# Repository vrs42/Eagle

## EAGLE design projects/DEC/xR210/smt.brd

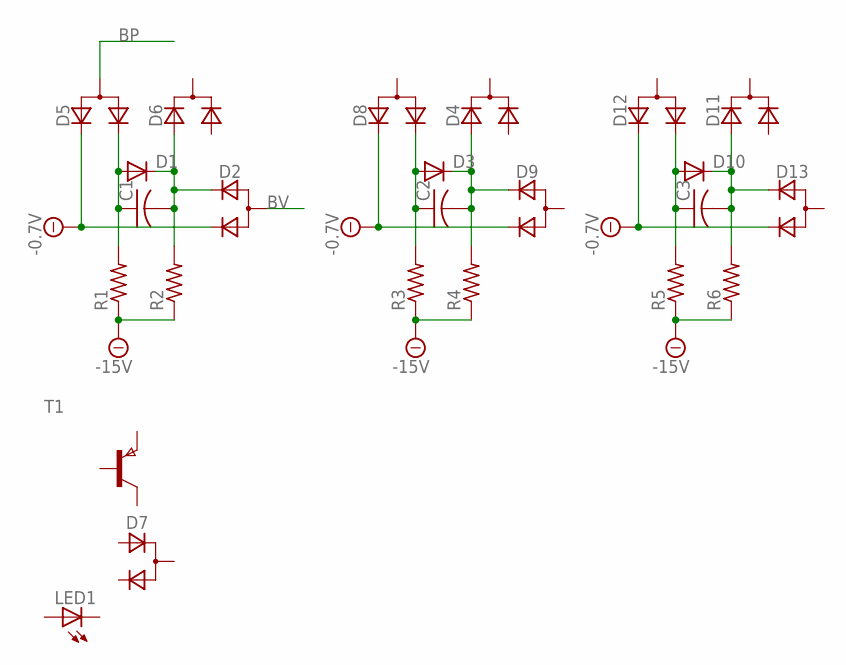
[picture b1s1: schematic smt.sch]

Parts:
C1, C2, C3: C-USC0603; C0603
D1, D3, D10: DIODE-SOD323-R; SOD323-R
D2, D5, D8, D9, D12, D13: D_2CSOT323; SOT323
D4, D6, D11: D_2ASOT323; SOT323
D7: D_ACACSOT323; SOT323
LED1: LEDCHIPLED_0603; CHIPLED_0603
R1, R2, R3, R4, R5, R6: R-US_R0603; R0603
T1: PNPSOT323; SOT323

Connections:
-1V: D2.3 (C2), D5.2 (C1), D8.2 (C1), D9.3 (C2), D12.2 (C1), D13.3 (C2)
-15V: R1.1, R2.1, R3.1, R4.1, R5.1, R6.1
BP: D5.1 (A)
BV: D2.1 (A)
unnamed: C1.1, D1.A, D5.3 (C2), R1.2
unnamed: C1.2, D1.C, D2.2 (C1), D6.2 (A1), R2.2
unnamed: C2.1, D3.A, D8.3 (C2), R3.2
unnamed: C2.2, D3.C, D4.2 (A1), D9.2 (C1), R4.2
unnamed: C3.1, D10.A, D12.3 (C2), R5.2
unnamed: C3.2, D10.C, D11.2 (A1), D13.2 (C1), R6.2

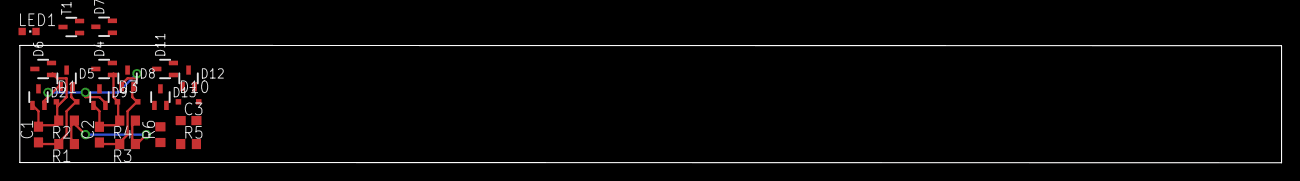
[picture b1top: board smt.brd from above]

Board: 2 copper layers, 136.7 x 12.7 mm, 24 parts (0 on the bottom side), 8 nets.

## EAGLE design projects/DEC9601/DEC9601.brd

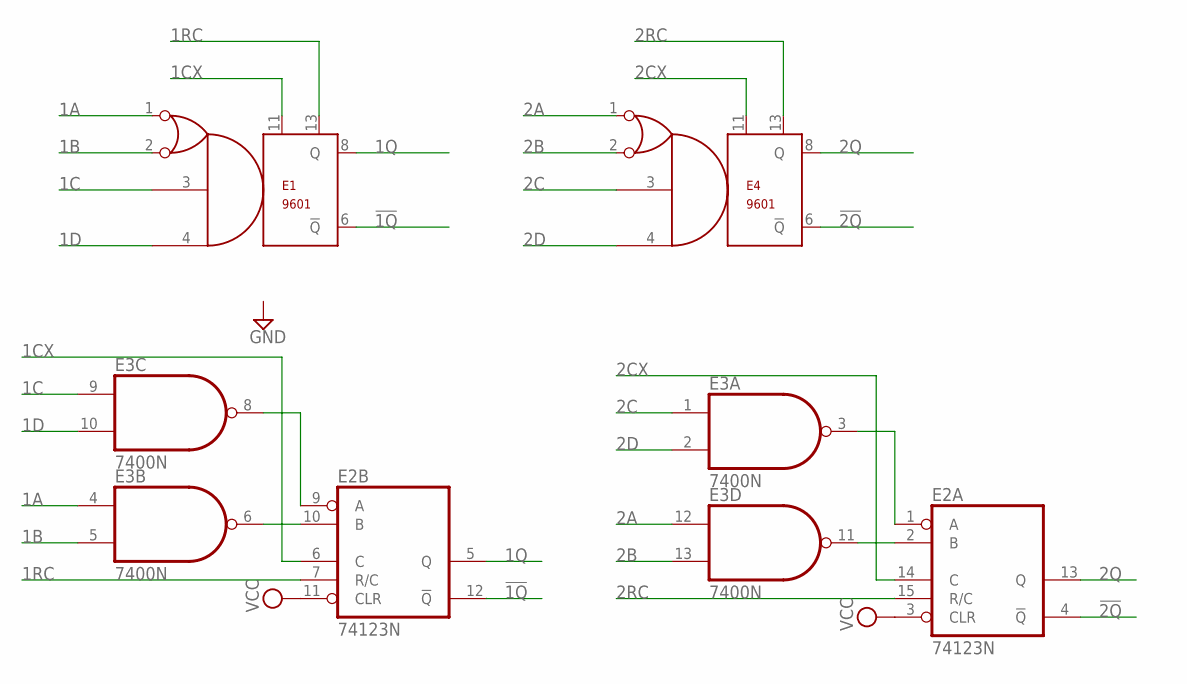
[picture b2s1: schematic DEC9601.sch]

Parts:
E1, E4: 9601; DIL14
E2: 74123N; DIL16
E3: 7400N; DIL14

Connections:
1A: E1.1, E3.4 (I0)
1B: E1.2, E3.5 (I1)
1C: E1.3, E3.9 (I0)
1CX: E1.11, E2.6 (C)
1D: E1.4, E3.10 (I1)
1Q: E1.8 (Q), E2.5 (Q)
1RC: E1.13, E2.7 (R/C)
2A: E3.12 (I0), E4.1
2B: E3.13 (I1), E4.2
2C: E3.1 (I0), E4.3
2CX: E2.14 (C), E4.11
2D: E3.2 (I1), E4.4
2Q: E2.13 (Q), E4.8 (Q)
2RC: E2.15 (R/C), E4.13
!1Q: E1.6 (!Q), E2.12 (!Q)
!2Q: E2.4 (!Q), E4.6 (!Q)
GND: E1.7 (GND), E2.8 (GND), E3.7 (GND), E4.7 (GND)
unnamed: E2.10 (B), E3.6 (O)
unnamed: E2.9 (A), E3.8 (O)
unnamed: E2.1 (A), E3.3 (O)
unnamed: E2.2 (B), E3.11 (O)
VCC: E1.14 (VCC), E2.3 (CLR), E2.11 (CLR), E2.16 (VCC), E3.14 (VCC), E4.14 (VCC)

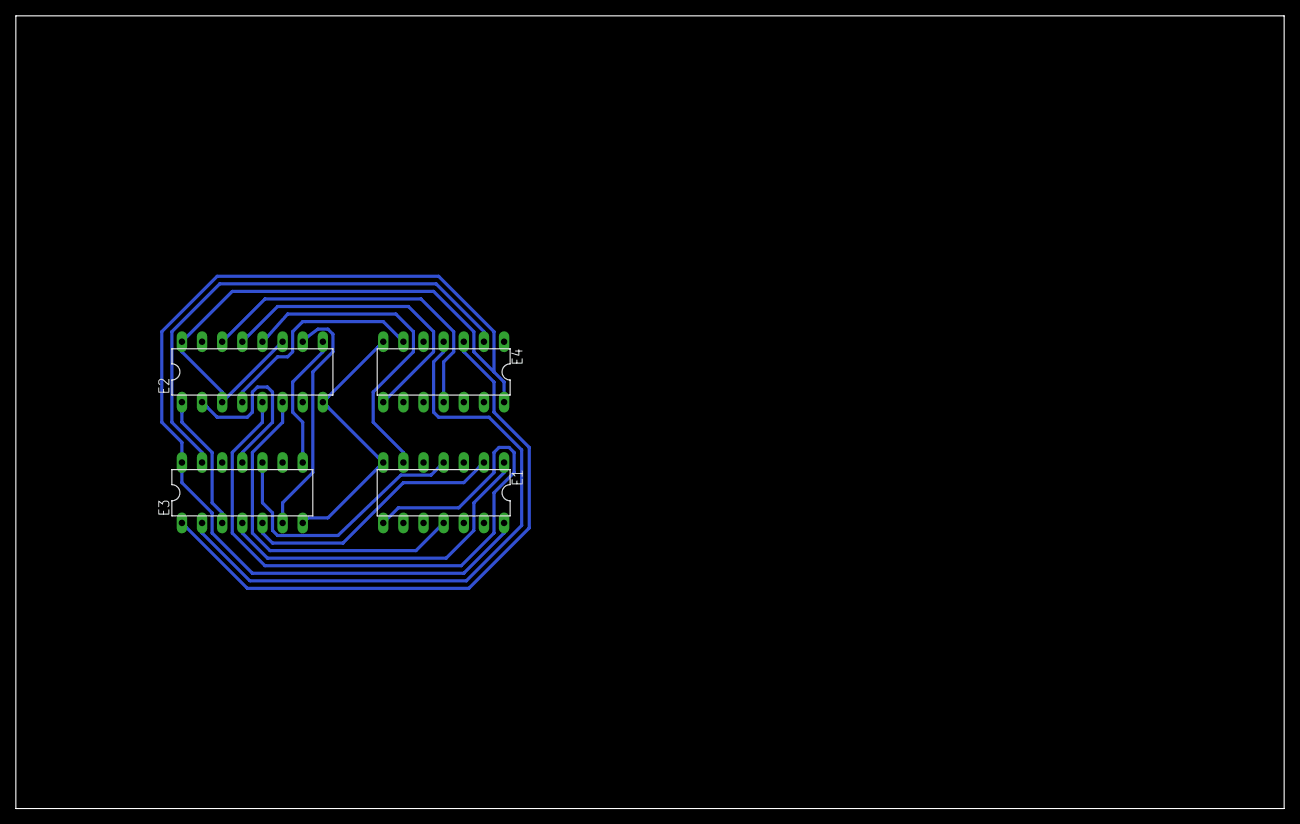
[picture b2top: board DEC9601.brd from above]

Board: 2 copper layers, 160.0 x 100.0 mm, 4 parts (0 on the bottom side), 22 nets.

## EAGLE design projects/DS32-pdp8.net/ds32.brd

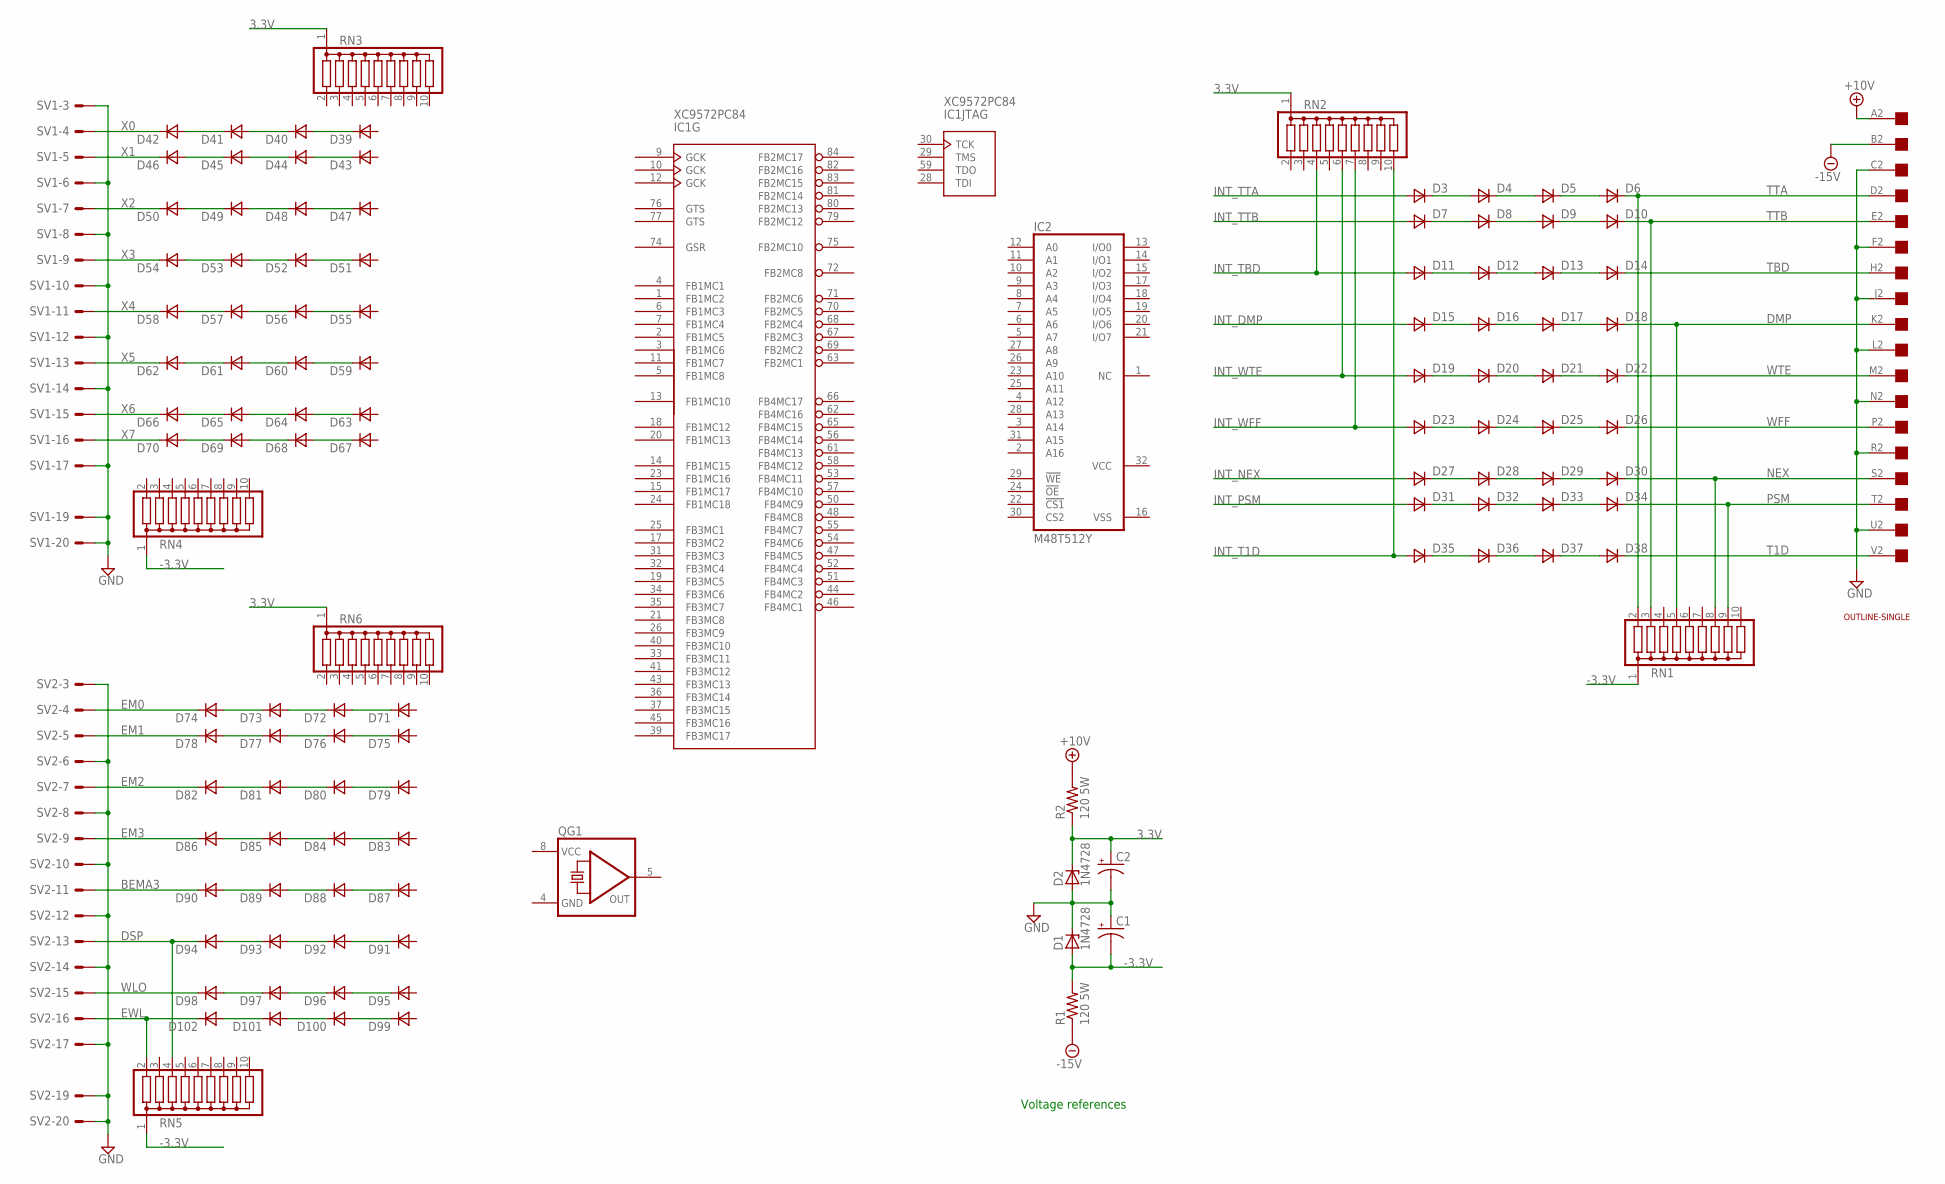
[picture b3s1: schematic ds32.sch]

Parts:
C1, C2: CPOL-USE15-5AXIAL; E15-5
D1, D2: 1N4728; DO41Z10
D3, D4, D5, D6, D7, D8, D9, D10, D11, D12, D13, D14, D15, D16, D17, D18, D19, D20, D21, D22, D23, D24, D25, D26, D27, D28, D29, D30, D31, D32, D33, D34, D35, D36, D37, D38, D39, D40, D41, D42, D43, D44, D45, D46, D47, D48, D49, D50, D51, D52, D53, D54, D55, D56, D57, D58, D59, D60, D61, D62, D63, D64, D65, D66, D67, D68, D69, D70, D71, D72, D73, D74, D75, D76, D77, D78, D79, D80, D81, D82, D83, D84, D85, D86, D87, D88, D89, D90, D91, D92, D93, D94, D95, D96, D97, D98, D99, D100, D101, D102: DSOD323; SOD323
IC1: XC9572PC84; PLCC-S84
IC2: M48T512Y; DIL32
QG1: QG5460; DIL08S
R1, R2: 120 5W; 0411/15
RN1, RN2, RN3, RN4, RN5, RN6: G09R; SIL10
SV1, SV2: ML20E; ML20
U$1: EDGE-1; EDGE-CON1
U$2: OUTLINE-SINGLE; SINGLE

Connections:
3.3V: C2.+, D2.C, R2.1, RN2.1, RN3.1, RN6.1
+10V: R2.2, U$1.A2
-3.3V: C1.-, D1.A, R1.2, RN1.1, RN4.1, RN5.1
-15V: R1.1, U$1.B2
BEMA3: D90.1 (C), SV2.11
DMP: D18.1 (C), RN1.5, U$1.K2
DSP: D94.1 (C), RN5.4, SV2.13
EM0: D74.1 (C), SV2.4
EM1: D78.1 (C), SV2.5
EM2: D82.1 (C), SV2.7
EM3: D86.1 (C), SV2.9
EWL: D102.1 (C), RN5.2, SV2.16
GND: C1.+, C2.-, D1.C, D2.A, IC1.8 (GND), IC1.16 (GND), IC1.27 (GND), IC1.42 (GND), IC1.49 (GND), IC1.60 (GND), QG1.4 (GND), SV1.3, SV1.6, SV1.8, SV1.10, SV1.12, SV1.14, SV1.17, SV1.19, SV1.20, SV2.3, SV2.6, SV2.8, SV2.10, SV2.12, SV2.14, SV2.17, SV2.19, SV2.20, U$1.C2, U$1.F2, U$1.J2, U$1.L2, U$1.N2, U$1.R2, U$1.U2
INT_DMP: D15.2 (A)
INT_NEX: D27.2 (A)
INT_PSM: D31.2 (A)
INT_T1D: D35.2 (A), RN2.10
INT_TBD: D11.2 (A), RN2.4
INT_TTA: D3.2 (A)
INT_TTB: D7.2 (A)
INT_WFF: D23.2 (A), RN2.7
INT_WTE: D19.2 (A), RN2.6
unnamed: D13.1 (C), D14.2 (A)
unnamed: D12.1 (C), D13.2 (A)
unnamed: D11.1 (C), D12.2 (A)
unnamed: D17.1 (C), D18.2 (A)
unnamed: D9.1 (C), D10.2 (A)
unnamed: D8.1 (C), D9.2 (A)
unnamed: D7.1 (C), D8.2 (A)
unnamed: D16.1 (C), D17.2 (A)
unnamed: D15.1 (C), D16.2 (A)
unnamed: D5.1 (C), D6.2 (A)
unnamed: D4.1 (C), D5.2 (A)
unnamed: D3.1 (C), D4.2 (A)
unnamed: D21.1 (C), D22.2 (A)
unnamed: D20.1 (C), D21.2 (A)
unnamed: D19.1 (C), D20.2 (A)
unnamed: D25.1 (C), D26.2 (A)
unnamed: D24.1 (C), D25.2 (A)
unnamed: D23.1 (C), D24.2 (A)
unnamed: D29.1 (C), D30.2 (A)
unnamed: D28.1 (C), D29.2 (A)
unnamed: D27.1 (C), D28.2 (A)
unnamed: D33.1 (C), D34.2 (A)
unnamed: D32.1 (C), D33.2 (A)
unnamed: D31.1 (C), D32.2 (A)
unnamed: D37.1 (C), D38.2 (A)
unnamed: D36.1 (C), D37.2 (A)
unnamed: D35.1 (C), D36.2 (A)
unnamed: D41.1 (C), D42.2 (A)
unnamed: D40.1 (C), D41.2 (A)
unnamed: D39.1 (C), D40.2 (A)
unnamed: D45.1 (C), D46.2 (A)
unnamed: D44.1 (C), D45.2 (A)
unnamed: D43.1 (C), D44.2 (A)
unnamed: D49.1 (C), D50.2 (A)
unnamed: D48.1 (C), D49.2 (A)
unnamed: D47.1 (C), D48.2 (A)
unnamed: D53.1 (C), D54.2 (A)
unnamed: D52.1 (C), D53.2 (A)
unnamed: D51.1 (C), D52.2 (A)
unnamed: D57.1 (C), D58.2 (A)
unnamed: D56.1 (C), D57.2 (A)
unnamed: D55.1 (C), D56.2 (A)
unnamed: D61.1 (C), D62.2 (A)
unnamed: D60.1 (C), D61.2 (A)
unnamed: D59.1 (C), D60.2 (A)
unnamed: D65.1 (C), D66.2 (A)
unnamed: D64.1 (C), D65.2 (A)
unnamed: D63.1 (C), D64.2 (A)
unnamed: D69.1 (C), D70.2 (A)
unnamed: D68.1 (C), D69.2 (A)
unnamed: D67.1 (C), D68.2 (A)
unnamed: D73.1 (C), D74.2 (A)
unnamed: D72.1 (C), D73.2 (A)
unnamed: D71.1 (C), D72.2 (A)
unnamed: D77.1 (C), D78.2 (A)
unnamed: D76.1 (C), D77.2 (A)
unnamed: D75.1 (C), D76.2 (A)
unnamed: D81.1 (C), D82.2 (A)
unnamed: D80.1 (C), D81.2 (A)
unnamed: D79.1 (C), D80.2 (A)
unnamed: D85.1 (C), D86.2 (A)
unnamed: D84.1 (C), D85.2 (A)
unnamed: D83.1 (C), D84.2 (A)
unnamed: D89.1 (C), D90.2 (A)
unnamed: D88.1 (C), D89.2 (A)
unnamed: D87.1 (C), D88.2 (A)
unnamed: D93.1 (C), D94.2 (A)
unnamed: D92.1 (C), D93.2 (A)
unnamed: D91.1 (C), D92.2 (A)
unnamed: D97.1 (C), D98.2 (A)
unnamed: D96.1 (C), D97.2 (A)
unnamed: D95.1 (C), D96.2 (A)
unnamed: D101.1 (C), D102.2 (A)
unnamed: D100.1 (C), D101.2 (A)
unnamed: D99.1 (C), D100.2 (A)
NEX: D30.1 (C), RN1.8, U$1.S2
PSM: D34.1 (C), RN1.9, U$1.T2
T1D: D38.1 (C), U$1.V2
TBD: D14.1 (C), U$1.H2
TTA: D6.1 (C), RN1.2, U$1.D2
TTB: D10.1 (C), RN1.3, U$1.E2
VCC: IC1.22 (VCC), IC1.38 (VCC), IC1.64 (VCC), IC1.73 (VCC), IC1.78 (VCC), IC2.32 (VCC), QG1.8 (VCC)
VSS: IC2.16 (VSS)
WFF: D26.1 (C), U$1.P2
WLO: D98.1 (C), SV2.15
WTE: D22.1 (C), U$1.M2
X0: D42.1 (C), SV1.4
X1: D46.1 (C), SV1.5
X2: D50.1 (C), SV1.7
X3: D54.1 (C), SV1.9
X4: D58.1 (C), SV1.11
X5: D62.1 (C), SV1.13
X6: D66.1 (C), SV1.15
X7: D70.1 (C), SV1.16

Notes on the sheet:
Voltage references

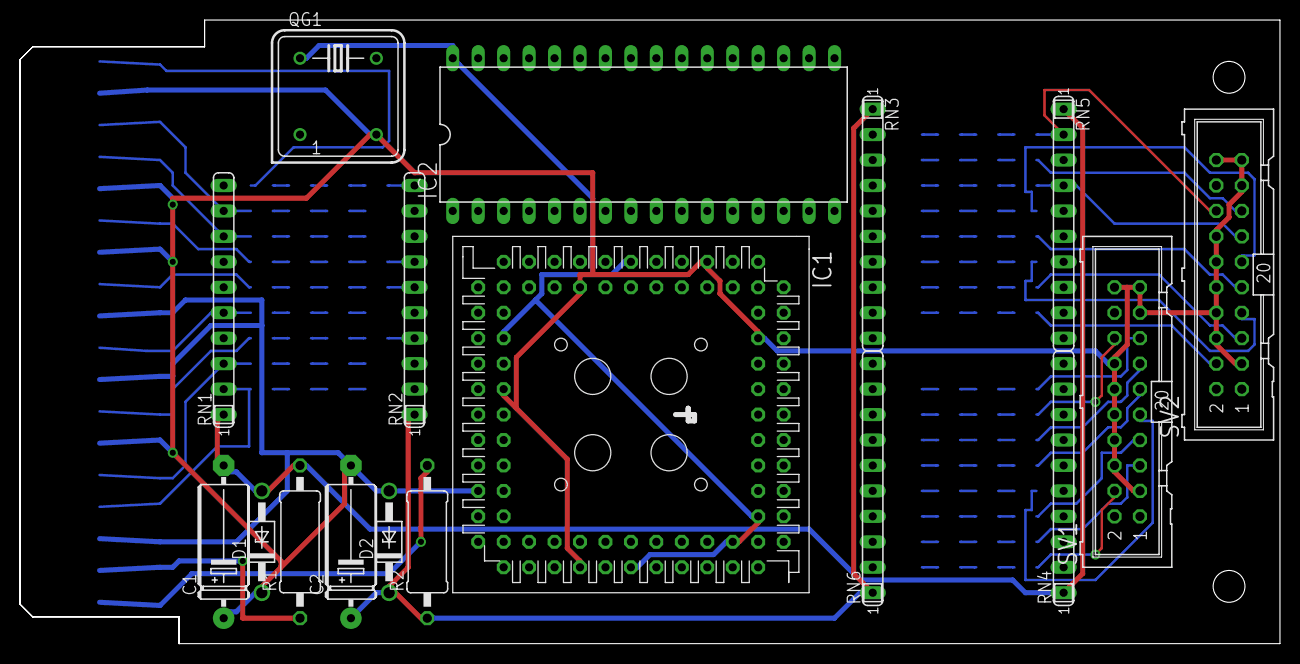
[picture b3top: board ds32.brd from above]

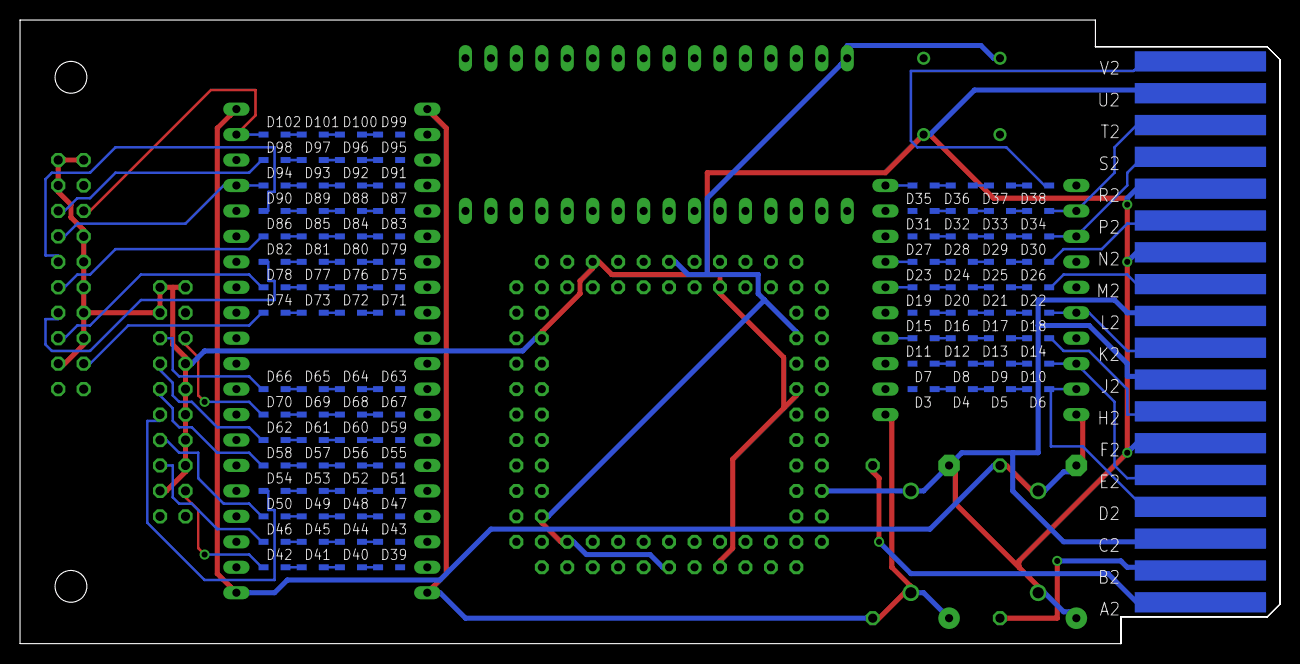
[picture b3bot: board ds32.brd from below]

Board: 2 copper layers, 125.7 x 62.2 mm, 119 parts (100 on the bottom side), 110 nets.

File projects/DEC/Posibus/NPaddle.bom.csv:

Comment,Designator,Footprint,PartNo
1N4148WS,D1,SOD323-W,C2128
1N4148WS,D2,SOD323-W,C2128
1N4148WS,D3,SOD323-W,C2128
1N4148WS,D4,SOD323-W,C2128
1N4148WS,D5,SOD323-W,C2128
1N4148WS,D6,SOD323-W,C2128
1N4148WS,D7,SOD323-W,C2128
1N4148WS,D8,SOD323-W,C2128
1N4148WS,D9,SOD323-W,C2128
1N4148WS,D10,SOD323-W,C2128
1N4148WS,D11,SOD323-W,C2128
1N4148WS,D12,SOD323-W,C2128
1N4148WS,D13,SOD323-W,C2128
1N4148WS,D14,SOD323-W,C2128
1N4148WS,D15,SOD323-W,C2128
1N4148WS,D16,SOD323-W,C2128
1N4148WS,D17,SOD323-W,C2128
1N4148WS,D18,SOD323-W,C2128
1N4148WS,D19,SOD323-W,C2128
1N4148WS,D20,SOD323-W,C2128
1N4148WS,D21,SOD323-W,C2128
1N4148WS,D22,SOD323-W,C2128
1N4148WS,D23,SOD323-W,C2128
1N4148WS,D24,SOD323-W,C2128
1N4148WS,D25,SOD323-W,C2128
1N4148WS,D26,SOD323-W,C2128
1N4148WS,D27,SOD323-W,C2128
1N4148WS,D28,SOD323-W,C2128
1N4148WS,D29,SOD323-W,C2128
1N4148WS,D30,SOD323-W,C2128
1N4148WS,D31,SOD323-W,C2128
1N4148WS,D32,SOD323-W,C2128
1N4148WS,D33,SOD323-W,C2128
1N4148WS,D34,SOD323-W,C2128
1N4148WS,D35,SOD323-W,C2128
1N4148WS,D36,SOD323-W,C2128
1N4148WS,D37,SOD323-W,C2128
1N4148WS,D38,SOD323-W,C2128
1N4148WS,D39,SOD323-W,C2128
1N4148WS,D40,SOD323-W,C2128
1N4148WS,D41,SOD323-W,C2128
1N4148WS,D42,SOD323-W,C2128
1N4148WS,D43,SOD323-W,C2128
1N4148WS,D44,SOD323-W,C2128
1N4148WS,D45,SOD323-W,C2128
1N4148WS,D46,SOD323-W,C2128
1N4148WS,D47,SOD323-W,C2128
1N4148WS,D48,SOD323-W,C2128
1N4148WS,D49,SOD323-W,C2128
1N4148WS,D50,SOD323-W,C2128
1N4148WS,D51,SOD323-W,C2128
1N4148WS,D52,SOD323-W,C2128
1N4148WS,D53,SOD323-W,C2128
1N4148WS,D54,SOD323-W,C2128
74LS240DW,U2,SO20W,C22449636
74LS240DW,U1,SO20W,C22449636
1N4148WS,D55,SOD323-W,C2128
1N4148WS,D56,SOD323-W,C2128
1N4148WS,D57,SOD323-W,C2128
1N4148WS,D58,SOD323-W,C2128
1N4148WS,D59,SOD323-W,C2128
1N4148WS,D60,SOD323-W,C2128
1N4148WS,D61,SOD323-W,C2128
1N4148WS,D62,SOD323-W,C2128
1N4148WS,D63,SOD323-W,C2128
1N4148WS,D64,SOD323-W,C2128
1N4148WS,D65,SOD323-W,C2128

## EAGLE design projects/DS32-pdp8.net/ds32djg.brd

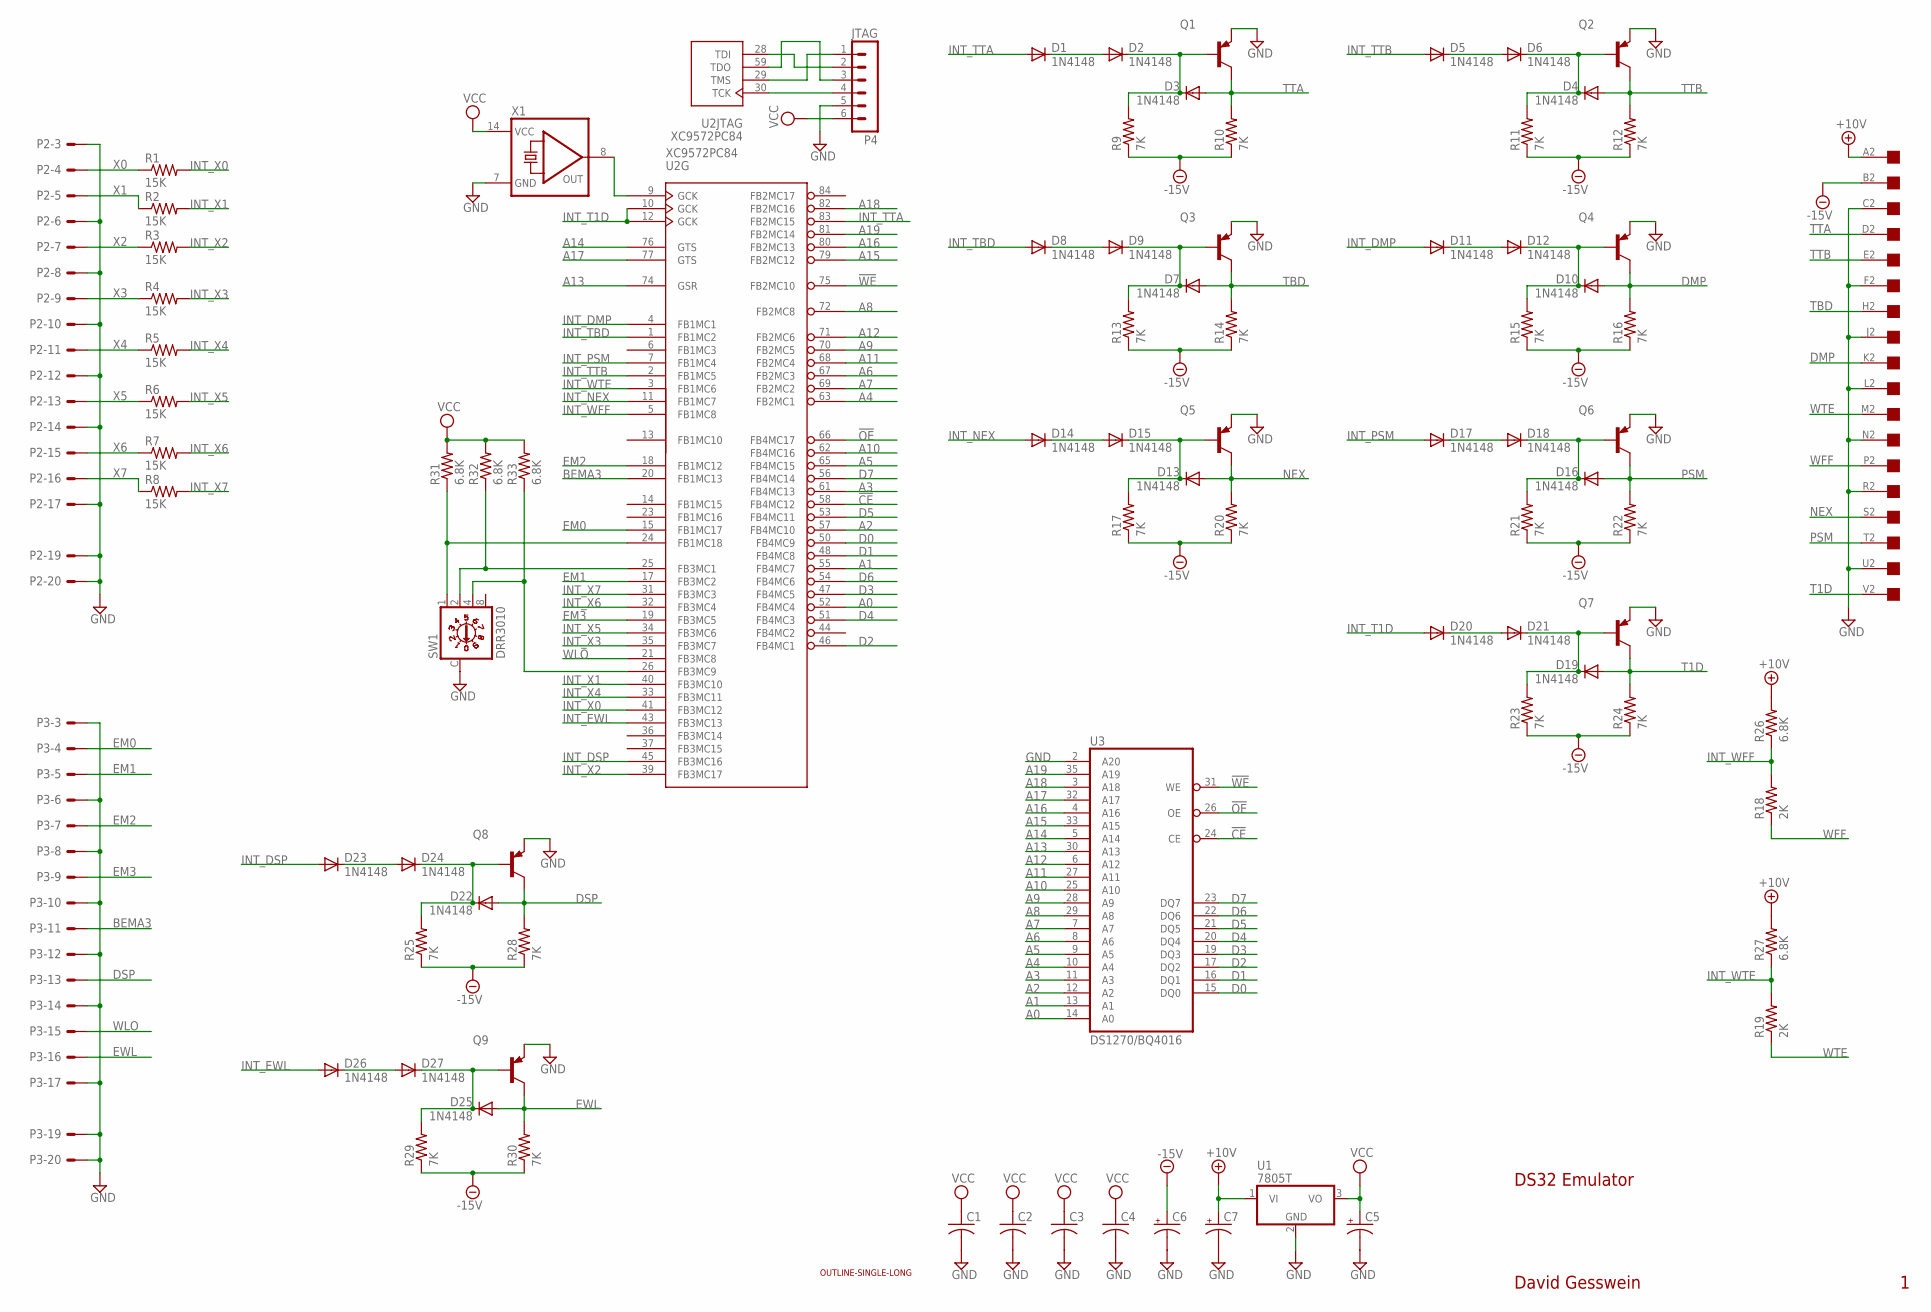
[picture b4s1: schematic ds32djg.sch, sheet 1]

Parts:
C1, C2, C3, C4: C-US050-025X075; C050-025X075
C5, C6, C7: CPOL-USE15-5AXIAL; E15-5
D1, D2, D3, D4, D5, D6, D7, D8, D9, D10, D11, D12, D13, D14, D15, D16, D17, D18, D19, D20, D21, D22, D23, D24, D25, D26, D27: 1N4148; DO35-10
P1: EDGE-1; EDGE-CON1
P2, P3: ML20E; ML20
P4: JTAG; MA06-1
Q1, Q2, Q3, Q4, Q5, Q6, Q7, Q8, Q9: -PNP-TO92/; TO92/
R1, R2, R3, R4, R5, R6, R7, R8: 15K; 0207/10
R9, R10, R11, R12, R13, R14, R15, R16, R17, R20, R21, R22, R23, R24, R25, R28, R29, R30: 7K; 0207/10
R18, R19: 2K; 0207/10
R26, R27, R31, R32, R33: 6.8K; 0207/10
SW1: DRR3010
U1: 7805T; TO220H
U2: XC9572PC84; PLCC-S84
U3: DS1270/BQ4016; MIL740EXT36
U$3: OUTLINE-SINGLE-LONG; SINGLE-LONG
X1: QG5860; DIL14S

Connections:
!CE: U2.58 (FB4MC12), U3.24 (CE)
!OE: U2.66 (FB4MC17), U3.26 (OE)
!WE: U2.75 (FB2MC10), U3.31 (WE)
+10V: C7.+, P1.A2, R26.2, R27.2, U1.1 (VI)
-15V: C6.+, P1.B2, R9.1, R10.1, R11.1, R12.1, R13.1, R14.1, R15.1, R16.1, R17.1, R20.1, R21.1, R22.1, R23.1, R24.1, R25.1, R28.1, R29.1, R30.1
A0: U2.52 (FB4MC4), U3.14 (A0)
A1: U2.55 (FB4MC7), U3.13 (A1)
A2: U2.57 (FB4MC10), U3.12 (A2)
A3: U2.61 (FB4MC13), U3.11 (A3)
A4: U2.63 (FB2MC1), U3.10 (A4)
A5: U2.65 (FB4MC15), U3.9 (A5)
A6: U2.67 (FB2MC3), U3.8 (A6)
A7: U2.69 (FB2MC2), U3.7 (A7)
A8: U2.72 (FB2MC8), U3.29 (A8)
A9: U2.70 (FB2MC5), U3.28 (A9)
A10: U2.62 (FB4MC16), U3.25 (A10)
A11: U2.68 (FB2MC4), U3.27 (A11)
A12: U2.71 (FB2MC6), U3.6 (A12)
A13: U2.74 (GSR), U3.30 (A13)
A14: U2.76 (GTS), U3.5 (A14)
A15: U2.79 (FB2MC12), U3.33 (A15)
A16: U2.80 (FB2MC13), U3.4 (A16)
A17: U2.77 (GTS), U3.32 (A17)
A18: U2.82 (FB2MC16), U3.3 (A18)
A19: U2.81 (FB2MC14), U3.35 (A19)
BEMA3: P3.11, U2.20 (FB1MC13)
D0: U2.50 (FB4MC9), U3.15 (DQ0)
D1: U2.48 (FB4MC8), U3.16 (DQ1)
D2: U2.46 (FB4MC1), U3.17 (DQ2)
D3: U2.47 (FB4MC5), U3.19 (DQ3)
D4: U2.51 (FB4MC3), U3.20 (DQ4)
D5: U2.53 (FB4MC11), U3.21 (DQ5)
D6: U2.54 (FB4MC6), U3.22 (DQ6)
D7: U2.56 (FB4MC14), U3.23 (DQ7)
DMP: D10.A, P1.K2, Q4.3 (C), R16.2
DSP: D22.A, P3.13, Q8.3 (C), R28.2
EM0: P3.4, U2.15 (FB1MC17)
EM1: P3.5, U2.17 (FB3MC2)
EM2: P3.7, U2.18 (FB1MC12)
EM3: P3.9, U2.19 (FB3MC5)
EWL: D25.A, P3.16, Q9.3 (C), R30.2
GND: C1.2, C2.2, C3.2, C4.2, C5.-, C6.-, C7.-, P1.C2, P1.F2, P1.J2, P1.L2, P1.N2, P1.R2, P1.U2, P2.3, P2.6, P2.8, P2.10, P2.12, P2.14, P2.17, P2.19, P2.20, P3.3, P3.6, P3.8, P3.10, P3.12, P3.14, P3.17, P3.19, P3.20, P4.5, Q1.1 (E), Q2.1 (E), Q3.1 (E), Q4.1 (E), Q5.1 (E), Q6.1 (E), Q7.1 (E), Q8.1 (E), Q9.1 (E), SW1.C, U1.2 (GND), U2.8 (GND), U2.16 (GND), U2.27 (GND), U2.42 (GND), U2.49 (GND), U2.60 (GND), U3.2 (A20), U3.18 (GND), X1.7 (GND)
INT_DMP: D11.A, U2.4 (FB1MC1)
INT_DSP: D23.A, U2.45 (FB3MC16)
INT_EWL: D26.A, U2.43 (FB3MC13)
INT_NEX: D14.A, U2.11 (FB1MC7)
INT_PSM: D17.A, U2.7 (FB1MC4)
INT_T1D: D20.A, U2.10 (GCK), U2.12 (GCK)
INT_TBD: D8.A, U2.1 (FB1MC2)
INT_TTA: D1.A, U2.83 (FB2MC15)
INT_TTB: D5.A, U2.2 (FB1MC5)
INT_WFF: R18.2, R26.1, U2.5 (FB1MC8)
INT_WTE: R19.2, R27.1, U2.3 (FB1MC6)
INT_X0: R1.2, U2.41 (FB3MC12)
INT_X1: R2.2, U2.40 (FB3MC10)
INT_X2: R3.2, U2.39 (FB3MC17)
INT_X3: R4.2, U2.35 (FB3MC7)
INT_X4: R5.2, U2.33 (FB3MC11)
INT_X5: R6.2, U2.34 (FB3MC6)
INT_X6: R7.2, U2.32 (FB3MC4)
INT_X7: R8.2, U2.31 (FB3MC3)
unnamed: P4.1, U2.29 (TMS)
unnamed: P4.2, U2.28 (TDI)
unnamed: P4.4, U2.30 (TCK)
unnamed: P4.3, U2.59 (TDO)
unnamed: U2.9 (GCK), X1.8 (OUT)
unnamed: D1.C, D2.A
unnamed: D2.C, D3.C, Q1.2 (B), R9.2
unnamed: D23.C, D24.A
unnamed: D22.C, D24.C, Q8.2 (B), R25.2
unnamed: D5.C, D6.A
unnamed: D4.C, D6.C, Q2.2 (B), R11.2
unnamed: D26.C, D27.A
unnamed: D25.C, D27.C, Q9.2 (B), R29.2
unnamed: D8.C, D9.A
unnamed: D7.C, D9.C, Q3.2 (B), R13.2
unnamed: R31.1, SW1.1, U2.24 (FB1MC18)
unnamed: D11.C, D12.A
unnamed: D10.C, D12.C, Q4.2 (B), R15.2
unnamed: R32.1, SW1.2, U2.25 (FB3MC1)
unnamed: R33.1, SW1.4, U2.26 (FB3MC9)
unnamed: D14.C, D15.A
unnamed: D13.C, D15.C, Q5.2 (B), R17.2
unnamed: D17.C, D18.A
unnamed: D16.C, D18.C, Q6.2 (B), R21.2
unnamed: D20.C, D21.A
unnamed: D19.C, D21.C, Q7.2 (B), R23.2
NEX: D13.A, P1.S2, Q5.3 (C), R20.2
PSM: D16.A, P1.T2, Q6.3 (C), R22.2
T1D: D19.A, P1.V2, Q7.3 (C), R24.2
TBD: D7.A, P1.H2, Q3.3 (C), R14.2
TTA: D3.A, P1.D2, Q1.3 (C), R10.2
TTB: D4.A, P1.E2, Q2.3 (C), R12.2
VCC: C1.1, C2.1, C3.1, C4.1, C5.+, P4.6, R31.2, R32.2, R33.2, U1.3 (VO), U2.22 (VCC), U2.38 (VCC), U2.64 (VCC), U2.73 (VCC), U2.78 (VCC), U3.36 (VCC), X1.14 (VCC)
WFF: P1.P2, R18.1
WLO: P3.15, U2.21 (FB3MC8)
WTE: P1.M2, R19.1
X0: P2.4, R1.1
X1: P2.5, R2.1
X2: P2.7, R3.1
X3: P2.9, R4.1
X4: P2.11, R5.1
X5: P2.13, R6.1
X6: P2.15, R7.1
X7: P2.16, R8.1

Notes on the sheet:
DS32 Emulator
David Gesswein

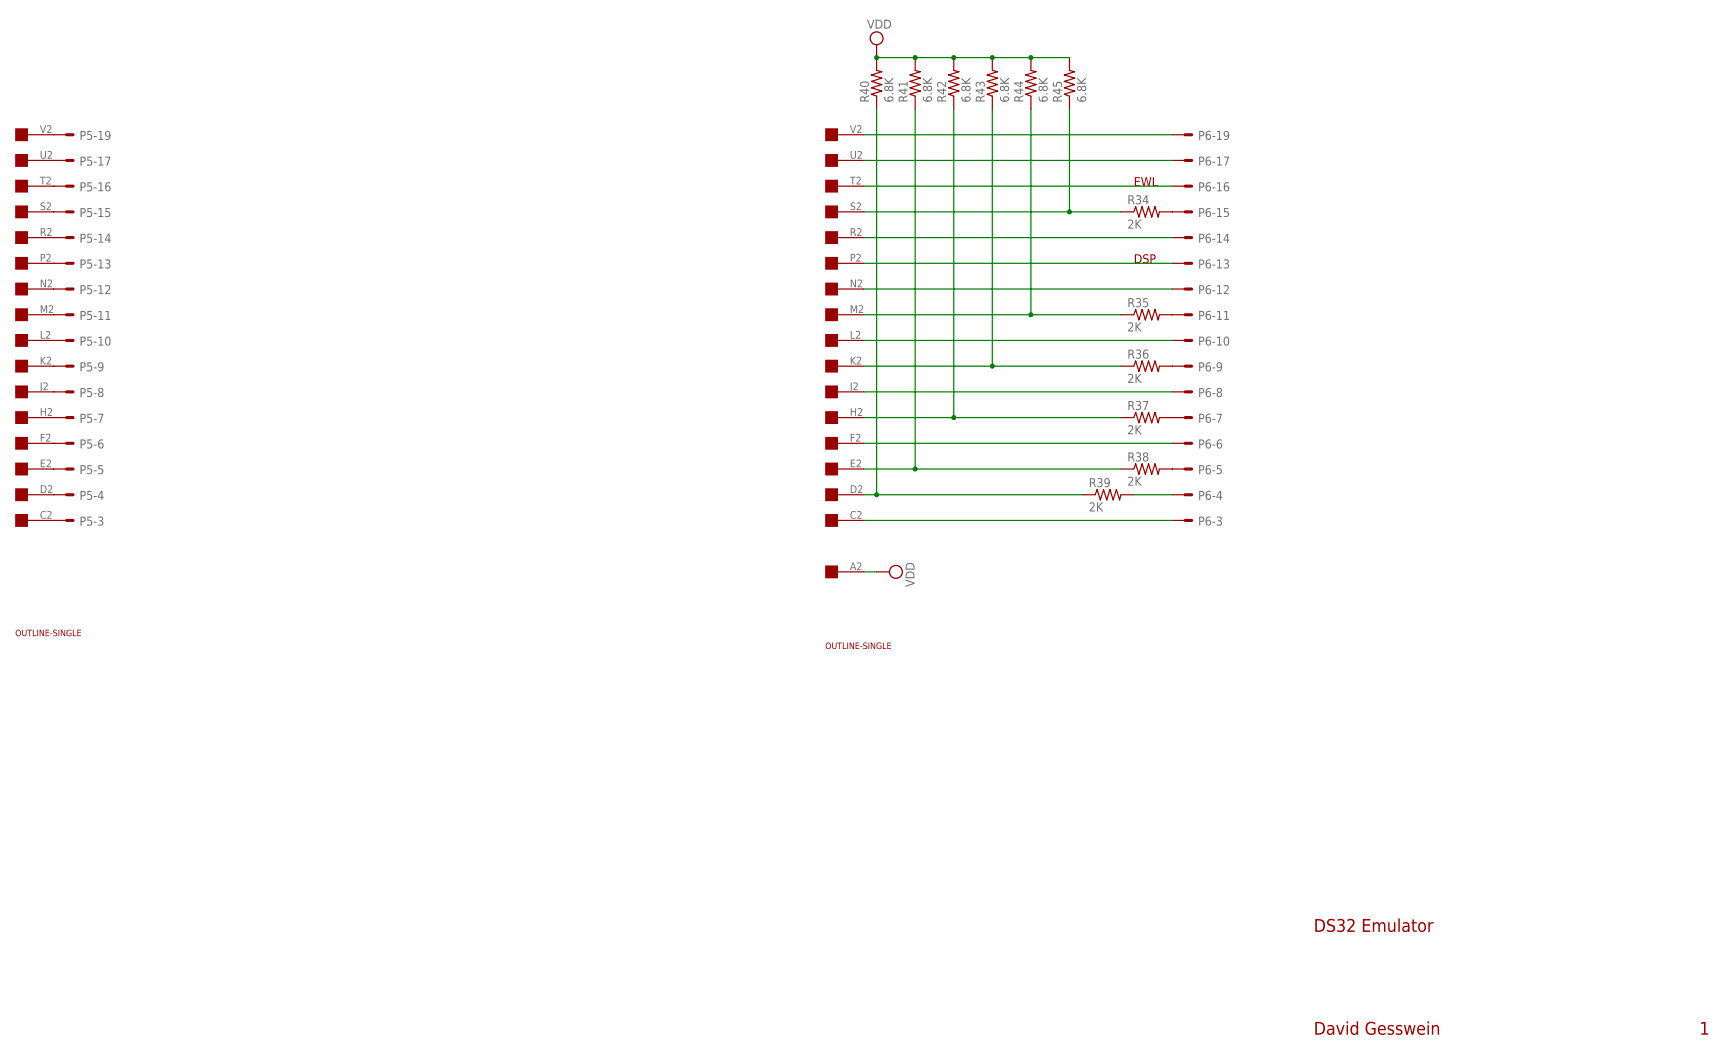
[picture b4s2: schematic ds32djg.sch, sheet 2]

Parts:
P5, P6: ML20E; ML20
R34, R35, R36, R37, R38, R39: 2K; 0207/10
R40, R41, R42, R43, R44, R45: 6.8K; 0207/10
U$1, U$2: EDGE-1; EDGE-CON1
U$4, U$5: OUTLINE-SINGLE; SINGLE

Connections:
unnamed: P6.3, U$2.C2
unnamed: P5.3, U$1.C2
unnamed: P5.4, U$1.D2
unnamed: P5.5, U$1.E2
unnamed: P5.6, U$1.F2
unnamed: P5.7, U$1.H2
unnamed: P5.8, U$1.J2
unnamed: P5.9, U$1.K2
unnamed: P5.10, U$1.L2
unnamed: P5.11, U$1.M2
unnamed: P5.12, U$1.N2
unnamed: P5.13, U$1.P2
unnamed: P5.14, U$1.R2
unnamed: P5.15, U$1.S2
unnamed: P5.16, U$1.T2
unnamed: P5.17, U$1.U2
unnamed: P5.19, U$1.V2
unnamed: P6.6, U$2.F2
unnamed: P6.8, U$2.J2
unnamed: P6.10, U$2.L2
unnamed: P6.12, U$2.N2
unnamed: P6.14, U$2.R2
unnamed: P6.19, U$2.V2
unnamed: P6.17, U$2.U2
unnamed: P6.16, U$2.T2
unnamed: P6.13, U$2.P2
unnamed: P6.15, R34.2
unnamed: P6.11, R35.2
unnamed: P6.9, R36.2
unnamed: P6.7, R37.2
unnamed: P6.5, R38.2
unnamed: P6.4, R39.2
unnamed: R39.1, R40.1, U$2.D2
unnamed: R38.1, R41.1, U$2.E2
unnamed: R37.1, R42.1, U$2.H2
unnamed: R36.1, R43.1, U$2.K2
unnamed: R35.1, R44.1, U$2.M2
unnamed: R34.1, R45.1, U$2.S2
VDD: R40.2, R41.2, R42.2, R43.2, R44.2, R45.2, U$2.A2

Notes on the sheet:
DSP
EWL
DS32 Emulator
David Gesswein

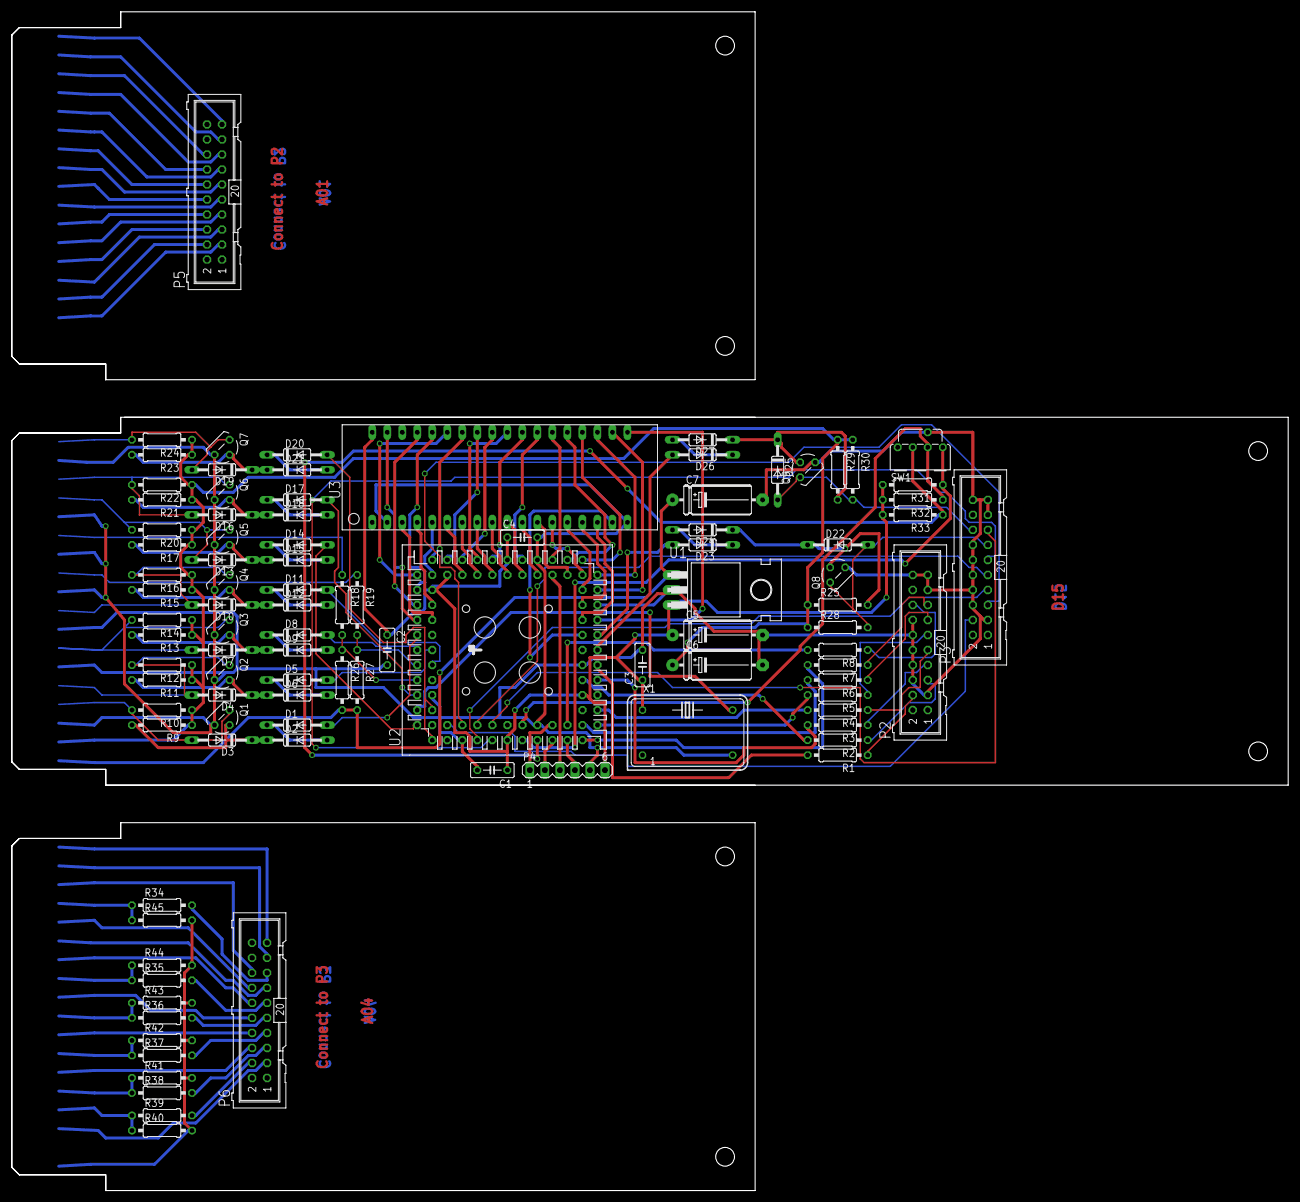
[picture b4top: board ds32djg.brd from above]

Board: 2 copper layers, 215.9 x 199.4 mm, 104 parts (0 on the bottom side), 144 nets.

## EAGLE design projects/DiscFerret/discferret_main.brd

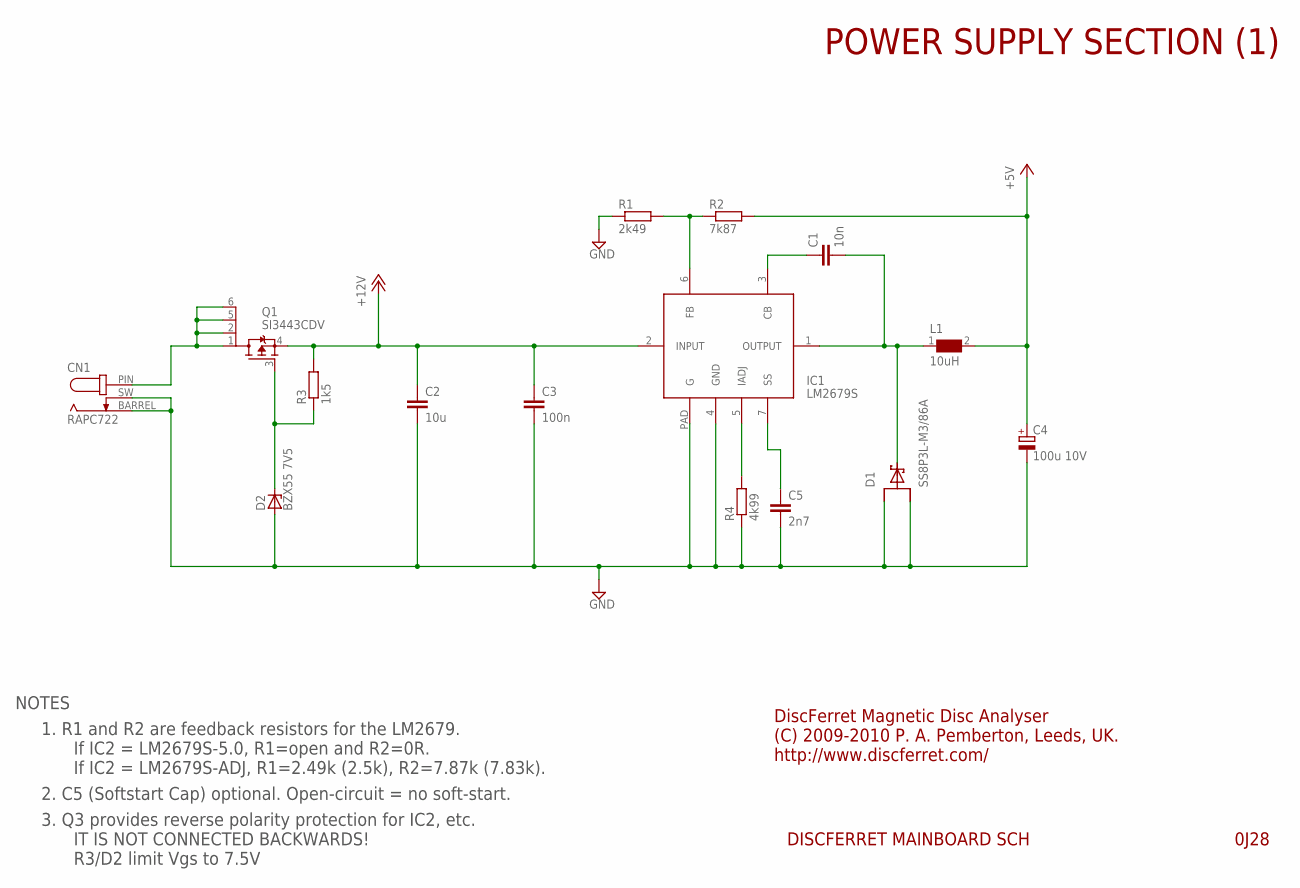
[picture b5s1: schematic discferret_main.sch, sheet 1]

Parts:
C1: 10n; C0603
C2: 10u; C0805
C3: 100n; C0603
C4: 100u 10V; SMC_D
C5: 2n7; C0805
CN1: RAPC722; RAPC722NT
D1: SS8P3L-M3/86A; TO277A_SMPC_LARGEPAD
D2: BZX55 7V5; DO35Z10
IC1: LM2679S; TO263-7
L1: 10uH; WE-PD_L/LS/XL/XXL
Q1: SI3443CDV; TSOP6_VISHAY_LARGEPAD
R1: 2k49; R0805
R2: 7k87; R0805
R3: 1k5; R0805
R4: 4k99; R0805

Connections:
+5V: C4.+, L1.2, R2.2; also elsewhere on the board
+12V: C2.1, C3.1, IC1.2 (INPUT), Q1.4 (S), R3.2; also elsewhere on the board
GND: C2.2, C3.2, C4.-, C5.2, CN1.BARREL (BAR), CN1.SW, D1.1 (A1), D1.2 (A2), D2.A, IC1.4 (GND), IC1.PAD (G), R1.1, R4.1; also elsewhere on the board
unnamed: CN1.PIN, Q1.1 (D1), Q1.2 (D2), Q1.5 (D3), Q1.6 (D4)
unnamed: IC1.5 (IADJ), R4.2
unnamed: C1.1, IC1.3 (CB)
unnamed: C5.1, IC1.7 (SS)
unnamed: C1.2, D1.K (C), IC1.1 (OUTPUT), L1.1
unnamed: D2.C, Q1.3 (G), R3.1
unnamed: IC1.6 (FB), R1.2, R2.1

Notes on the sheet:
DiscFerret Magnetic Disc Analyser
0J28
DISCFERRET MAINBOARD SCH
(C) 2009-2010 P. A. Pemberton, Leeds, UK.
http://www.discferret.com/
POWER SUPPLY SECTION (1)
NOTES
1. R1 and R2 are feedback resistors for the LM2679.
If IC2 = LM2679S-5.0, R1=open and R2=0R.
If IC2 = LM2679S-ADJ, R1=2.49k (2.5k), R2=7.87k (7.83k).
2. C5 (Softstart Cap) optional. Open-circuit = no soft-start.
3. Q3 provides reverse polarity protection for IC2, etc.
IT IS NOT CONNECTED BACKWARDS!
R3/D2 limit Vgs to 7.5V

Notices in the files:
projects/DiscFerret/discferret_main.brd:
(C) 2010 P A Pemberton
